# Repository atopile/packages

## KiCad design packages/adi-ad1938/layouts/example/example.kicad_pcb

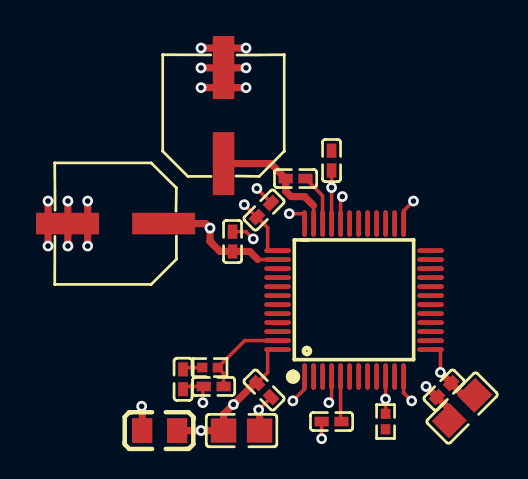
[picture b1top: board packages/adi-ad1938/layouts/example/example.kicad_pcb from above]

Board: 2 copper layers, 17 parts (0 on the bottom side), 8 nets.

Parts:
C1, C5, C6, C7, C8, C9, C12: 100nF ±10% 16V X7R; C0402
C2, C13: 47µF ±20% 35V; CAP-SMD_BD6.3-L6.6-W6.6-LS7.6-FD
C3, C4: 10µF ±10% 25V X5R; C0805
C10: 5.6nF ±10% 50V X7R; C0402
C11: 390pF ±10% 50V X7R; C0402
L1: 10nH ±5% 300mA 300mΩ; L0805
R1: 560Ω ±1% 62.5mW; R0402
R2: 100kΩ ±1% 62.5mW; R0402
U1: LQFP-48_L7.0-W7.0-P0.50-LS9.0-BL

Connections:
CM: C1.1, C2.1, U1.38
FILTR: C12.1, C13.1, U1.35
GND: C1.2, C2.2, C3.2, C4.2, C5.2, C6.2, C7.2, C8.2, C9.2, C10.2, C11.2, C12.2, C13.2, R2.2, U1.1, U1.4, U1.12, U1.25, U1.32, U1.34, U1.36
LF: C11.1, R1.1, U1.47
nPD_nRST: R2.1, U1.10
net: C10.1, R1.2
power_analog-VCC: C3.1, C5.1, C6.1, C7.1, C8.1, L1.2, U1.5, U1.33, U1.37, U1.48
power_io-VCC: C4.1, C9.1, L1.1, U1.13

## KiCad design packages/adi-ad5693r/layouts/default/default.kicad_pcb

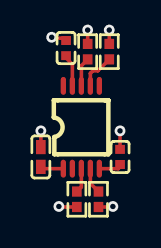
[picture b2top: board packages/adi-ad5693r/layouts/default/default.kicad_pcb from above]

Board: 2 copper layers, 8 parts (0 on the bottom side), 8 nets.

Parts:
C1, C3: 1F; C0402
C2: 9.999F; C0402
R1, R2, R3: 10000Ω; R0402
R4: 100000Ω; R0402
U1: MSOP-10_L3.0-W3.0-P0.50-LS4.9-BL

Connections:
SCL: R1.1, U1.7
SDA: R2.1, U1.8
hv: C1.1, C2.1, R4.2, U1.1
i2c-hv: R1.2, R2.2, U1.2
lv: C1.2, C2.2, C3.2, R3.2, U1.5, U1.6
nLDAC: R3.1, U1.4
nRESET: R4.1, U1.3
vref_cap-power-hv: C3.1, U1.9

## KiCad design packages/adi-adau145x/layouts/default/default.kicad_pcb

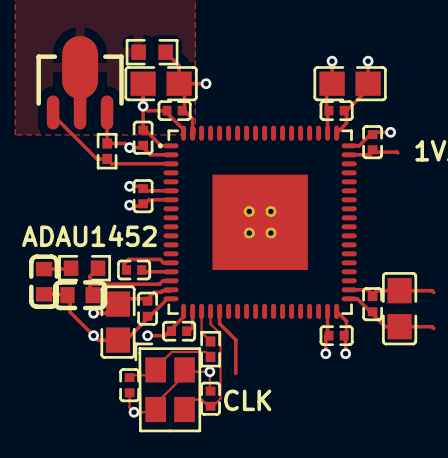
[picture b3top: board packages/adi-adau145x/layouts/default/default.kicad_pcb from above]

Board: 2 copper layers, 25 parts (0 on the bottom side), 10 nets.

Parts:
C1, C2, C3, C4, C5, C6, C7, C8, C9, C10: 100nF; C0402
C11, C12: 18pF; C0402
C13: 5.6nF; C0603
C14: 150pF; C0603
C15, C16, C17, C18: 10µF; C0805
Q1: SOT-89-3_L4.5-W2.5-P1.50-LS4.1-TR
R1: 100Ω; R0402
R2: 4.3kΩ; R0603
R3: 1kΩ; R0402
R4: 0Ω; R0603
U1: LFCSP-72_L10.0-W10.0-P0.50-LS10.2-BL-EP5.3
X1: CRYSTAL-SMD_4P-L3.2-W2.5-BL-2

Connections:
VDRIVE: Q1.3, R3.2, U1.3
XTALIN_MCLK: R1.1, U1.21
c1-power-hv: C13.1, R2.2
c2-power-hv: C14.1, R2.1, U1.16
c_load[0]-power-hv: C11.1, R1.2, X1.1
c_load[1]-power-hv: C12.1, U1.22, X1.3
collector: Q1.2, R4.1
hv: C1.1, C6.1, C7.1, C8.1, C9.1, C10.1, C13.2, C14.2, C15.1, C16.1, C18.1, Q1.1, R3.1, U1.2, U1.7, U1.15, U1.18, U1.38, U1.56
lv: C1.2, C2.2, C3.2, C4.2, C5.2, C6.2, C7.2, C8.2, C9.2, C10.2, C11.2, C12.2, C15.2, C16.2, C17.2, C18.2, U1.1, U1.6, U1.14, U1.17, U1.19, U1.25, U1.32, U1.33, U1.36, U1.37, U1.54, U1.55, U1.72, U1.73, X1.2, X1.4
power_digital-hv: C2.1, C3.1, C4.1, C5.1, C17.1, R4.2, U1.20, U1.35, U1.53, U1.71

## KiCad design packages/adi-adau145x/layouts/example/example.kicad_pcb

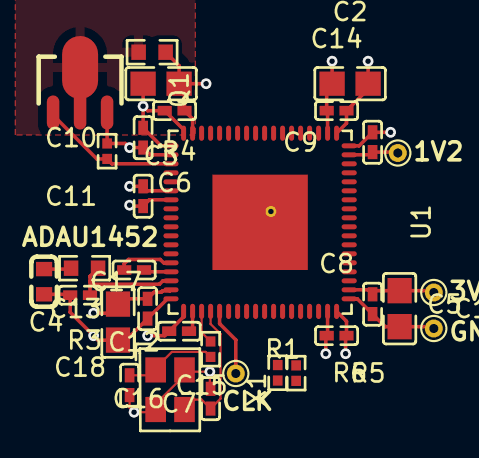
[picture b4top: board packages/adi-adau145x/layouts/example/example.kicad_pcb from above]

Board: 2 copper layers, 31 parts (0 on the bottom side), 13 nets.

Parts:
C1, C2, C3, C4: 10µF ±10% 16V X5R; C0805
C5, C6, C7, C8, C9, C10, C11, C12, C13, C14: 100nF ±10% 16V X7R; C0402
C15, C16: 20pF ±5% 50V C0G; C0402
C17: 5.6nF ±10% 50V X7R; C0603
C18: 150pF ±10% 50V X7R; C0402
Q1: SOT-89-3_L4.5-W2.5-P1.50-LS4.1-TR
R1: 100Ω ±1% 62.5mW; R0402
R2: 0Ω 100mW; R0603
R3: 4.3kΩ ±1% 100mW; R0603
R4: 1kΩ ±1% 62.5mW; R0402
R5, R6: 4.7kΩ ±1% 62.5mW; R0402
TP1, TP2, TP3, TP4: TestPoint_THTPad_D1.0mm_Drill0.5mm
U1: LFCSP-72_L10.0-W10.0-P0.50-LS10.2-BL-EP5.3
X1: CRYSTAL-SMD_4P-L3.2-W2.5-BL-2

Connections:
3V3: C1.1, C2.1, C4.1, C5.1, C10.1, C11.1, C12.1, C13.1, C14.1, C17.2, C18.2, Q1.1, R4.1, R5.2, R6.2, TP3.1, U1.2, U1.7, U1.15, U1.18, U1.32, U1.33, U1.38, U1.56
CLKOUT: TP1.1, U1.23
GND: C1.2, C2.2, C3.2, C4.2, C5.2, C6.2, C7.2, C8.2, C9.2, C10.2, C11.2, C12.2, C13.2, C14.2, C15.2, C16.2, TP2.1, U1.1, U1.6, U1.14, U1.17, U1.19, U1.25, U1.36, U1.37, U1.54, U1.55, U1.72, U1.73, X1.2, X1.4
MISO_SDA: R5.1, U1.30
PLLFILT: C18.1, R3.1, U1.16
SCLK_SCL: R6.1, U1.31
VDRIVE: Q1.3, R4.2, U1.3
XTALIN_MCLK: R1.1, U1.21
XTALOUT: C16.1, U1.22, X1.3
collector: Q1.2, R2.1
contact: C3.1, C6.1, C7.1, C8.1, C9.1, R2.2, TP4.1, U1.20, U1.35, U1.53, U1.71
dsp.pll_filter-net: C17.1, R3.2
nOE: C15.1, R1.2, X1.1

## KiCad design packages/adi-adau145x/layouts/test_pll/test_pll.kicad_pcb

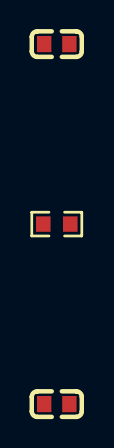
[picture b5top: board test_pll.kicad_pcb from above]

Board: 2 copper layers, 3 parts (0 on the bottom side), 3 nets, no tracks yet.

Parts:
C1: {5.03999999165535e-09..6.1600000083446495e-09}F; C0603
C2: {1.349999997764826e-10..1.650000002235174e-10}F; C0603
R1: 4300.0Ω; R0603

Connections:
NET_18928: C2.1, R1.1
NET_21488: C1.1, R1.2
NET_84480: C1.2, C2.2
